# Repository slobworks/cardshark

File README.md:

<b>Update 9/17/26:</b> Big gaggle of minor changes all over. Bigger, better and cleaner PCB art on the front. Changed all those pesky 0603 0.1uF capacitors to 0805 to make them slightly less fiddly. Had to do some moderate rerouting to compensate - hopefully the 40MHz operation is not adversely affected.

CARDSHARK Tiburon v1.1 - MIT-Licensed, Open-Source Cirrus Logic CL-GD543x Based VLB VGA Card

As it says on the package. This VGA card for the VESA Local Bus supports a maximum memory size of 2MB, using traditional multiple-CAS FPM 256Kx16 SOJ memory. 70ns or faster memory is recommended, as is a CL-GD5434 chip for the fastest speed and least confusing build.
Created using KiCAD 8.0, updated for 10.0 (a thousand apologies if this breaks your older version!)

Features:
- Four layer PCB with cautiously laid ground pours, and judicious usage of stitching vias
- Beefy dedicated regulator providing analog DAC power, for further improved picture quality
- 2MB FPM memory with 64-bit data bus for CL-GD5434
- Compatible with CL-GD5430 and CL-GD5434
- Uses a 27C256-compatible UV PROM or EPROM chip for the BIOS
- Supports 40MHz VLB bus on motherboards that can actually handle that
- Mercifully short mode-switch delays on LCD monitors, unlike most vintage VGA chipsets (a Cirrus quality)
- Features my own hand-drawn artwork on back of board

Release History:
- Tiburon v1.1: Tons o' minor tweaks: bigger, better and cleaner PCB art on the front. Moved BIOS socket so I can reduce the ominous kink in the RGB traces. More forgiving 0805(2012 metric) footprints for the 0.1uF capacitors; you can still fit 0603s to them though. Moved some stuff around to try to get shorter ground loop paths when possible.
- Tiburon v1.0: First proper release.
- Tiburon Take 3 (internal): FINALLY we have a properly working VLB card... so long as you only use a GD5434 and 2MB of memory. One of the RAS lines got screwed, which gets overridden anyway when a GD5434 is used. Also some really minor bugs (wrong resistor values in a couple spots, easily fixed). At least it sure looks nice assembled, and so long as it's given a GD5434 with 2MB, it's a monster (of the good kind).
- Take 2 (internal): Almost worked. Major bugs all over the place. Barely functional.
- 0.1b: Major overhaul. Relaid everything, redid a lot of stuff that was broken and didn't work (if the previous version wasted your money... sorry! I feel like a prize horse's arse for uploading something so broken, as it is!)

Known Issues:
- Hand-soldering that PQFP-208 chip with all those thin little pins is a nightmare, even with hot air
- While generally very good, Mode 13h and EGA image quality isn't 100% perfect on LCD. Some extremely faint vertical lines, though generally much less pronounced than on extant cards; you will probably want to play with your RetroTINK's timings a bit (these seem to be timing related and not noise, as they are not visible at all in SVGA modes)
- EDO is ONLY supported on CL-GD5434-J-QC, but even then it does not improve performance at all. *NO* other versions support EDO, so don't waste money ordering EDO SOJ chips

Bill of Materials: (All passive parts are 0805/2012 metric unless otherwise indicated)
- 1x Cirrus Logic CL-GD5430 or CL-GD5434 PQFP-208 chip (watch out for fakes - they're everywhere)
- 1x SOIC-14 (3.9mm x 8.7mm P1.27mm) SN74F260DR or directly compatible part
- At least 2x, but up to 4x 256Kx16 dual-CAS Fast Page Mode (*NOT* EDO) SOJ-40 DRAM memory
- 1x 78M05 5V DPAK regulator (LF50 is compatible)
- 1x 14.318MHz DIP-14 CXO 4-pin through-hole oscillator
- 1x MMBT3904 SOT-23 NPN transistor
- 1x TL431DBZ SOT-23 programmable shunt reference
- 3x 11 ohm @ 100MHz ferrite beads (for RGB signals)
- 3x 100+ ohm @ 100MHz ferrite beads (for power rails)
- 2x 1x2 2.54mm THT pin headers + jumper caps
- 1x 2x3 1.27mm SMD pin header + jumper caps
- 4x 10pF 25/50v MLCC X5R/X7R ceramic capacitor
- 20x 0805(2012 metric) 0.1uF 25/50v MLCC X5R/X7R ceramic capacitor
- 4x 2.2uF 25/50v MLCC X5R/X7R ceramic capacitor
- 6x 10uF 25/50v MLCC X5R/X7R ceramic capacitor
- 1x 5mm 22uF 16V SMD electrolytic capacitor
- 1x 0 ohm SMD resistor (or a short snip of wire)
- 3x 0603(1608 metric) 10 ohm SMD resistors
- 1x 4x0603 33 ohm convex SMD resistor pack
- 2x 0603(1608 metric) 75 ohm SMD resistors
- 1x 4x0603 75 ohm convex SMD resistor pack
- 1x 100 ohm SMD resistor
- 3x 0603(1608 metric) 6.8K SMD resistors
- 2x 4x0603 6.8K ohm convex SMD resistor packs
- 1x 0603(1608 metric) 270-330 ohm SMD resistor, 1% thin film
- 2x 1K SMD resistors
- 1x DSUB-15-HD right angle through hole VGA connector (something akin to this: https://www.digikey.com/en/products/detail/assmann-wsw-components/A-HDF15A-KG-TAXB/1241905)
- 1x DIP-28 socket + 27C256 or compatible PROM/EEPROM/flash ROM chip for BIOS + BIOS file (figure that out yourself)

Provided under the terms of the MIT License.

As you can see I'm a bit of a neophyte when it comes to this GitHub stuff.
Expect this to change as I become more familiar with the platform.

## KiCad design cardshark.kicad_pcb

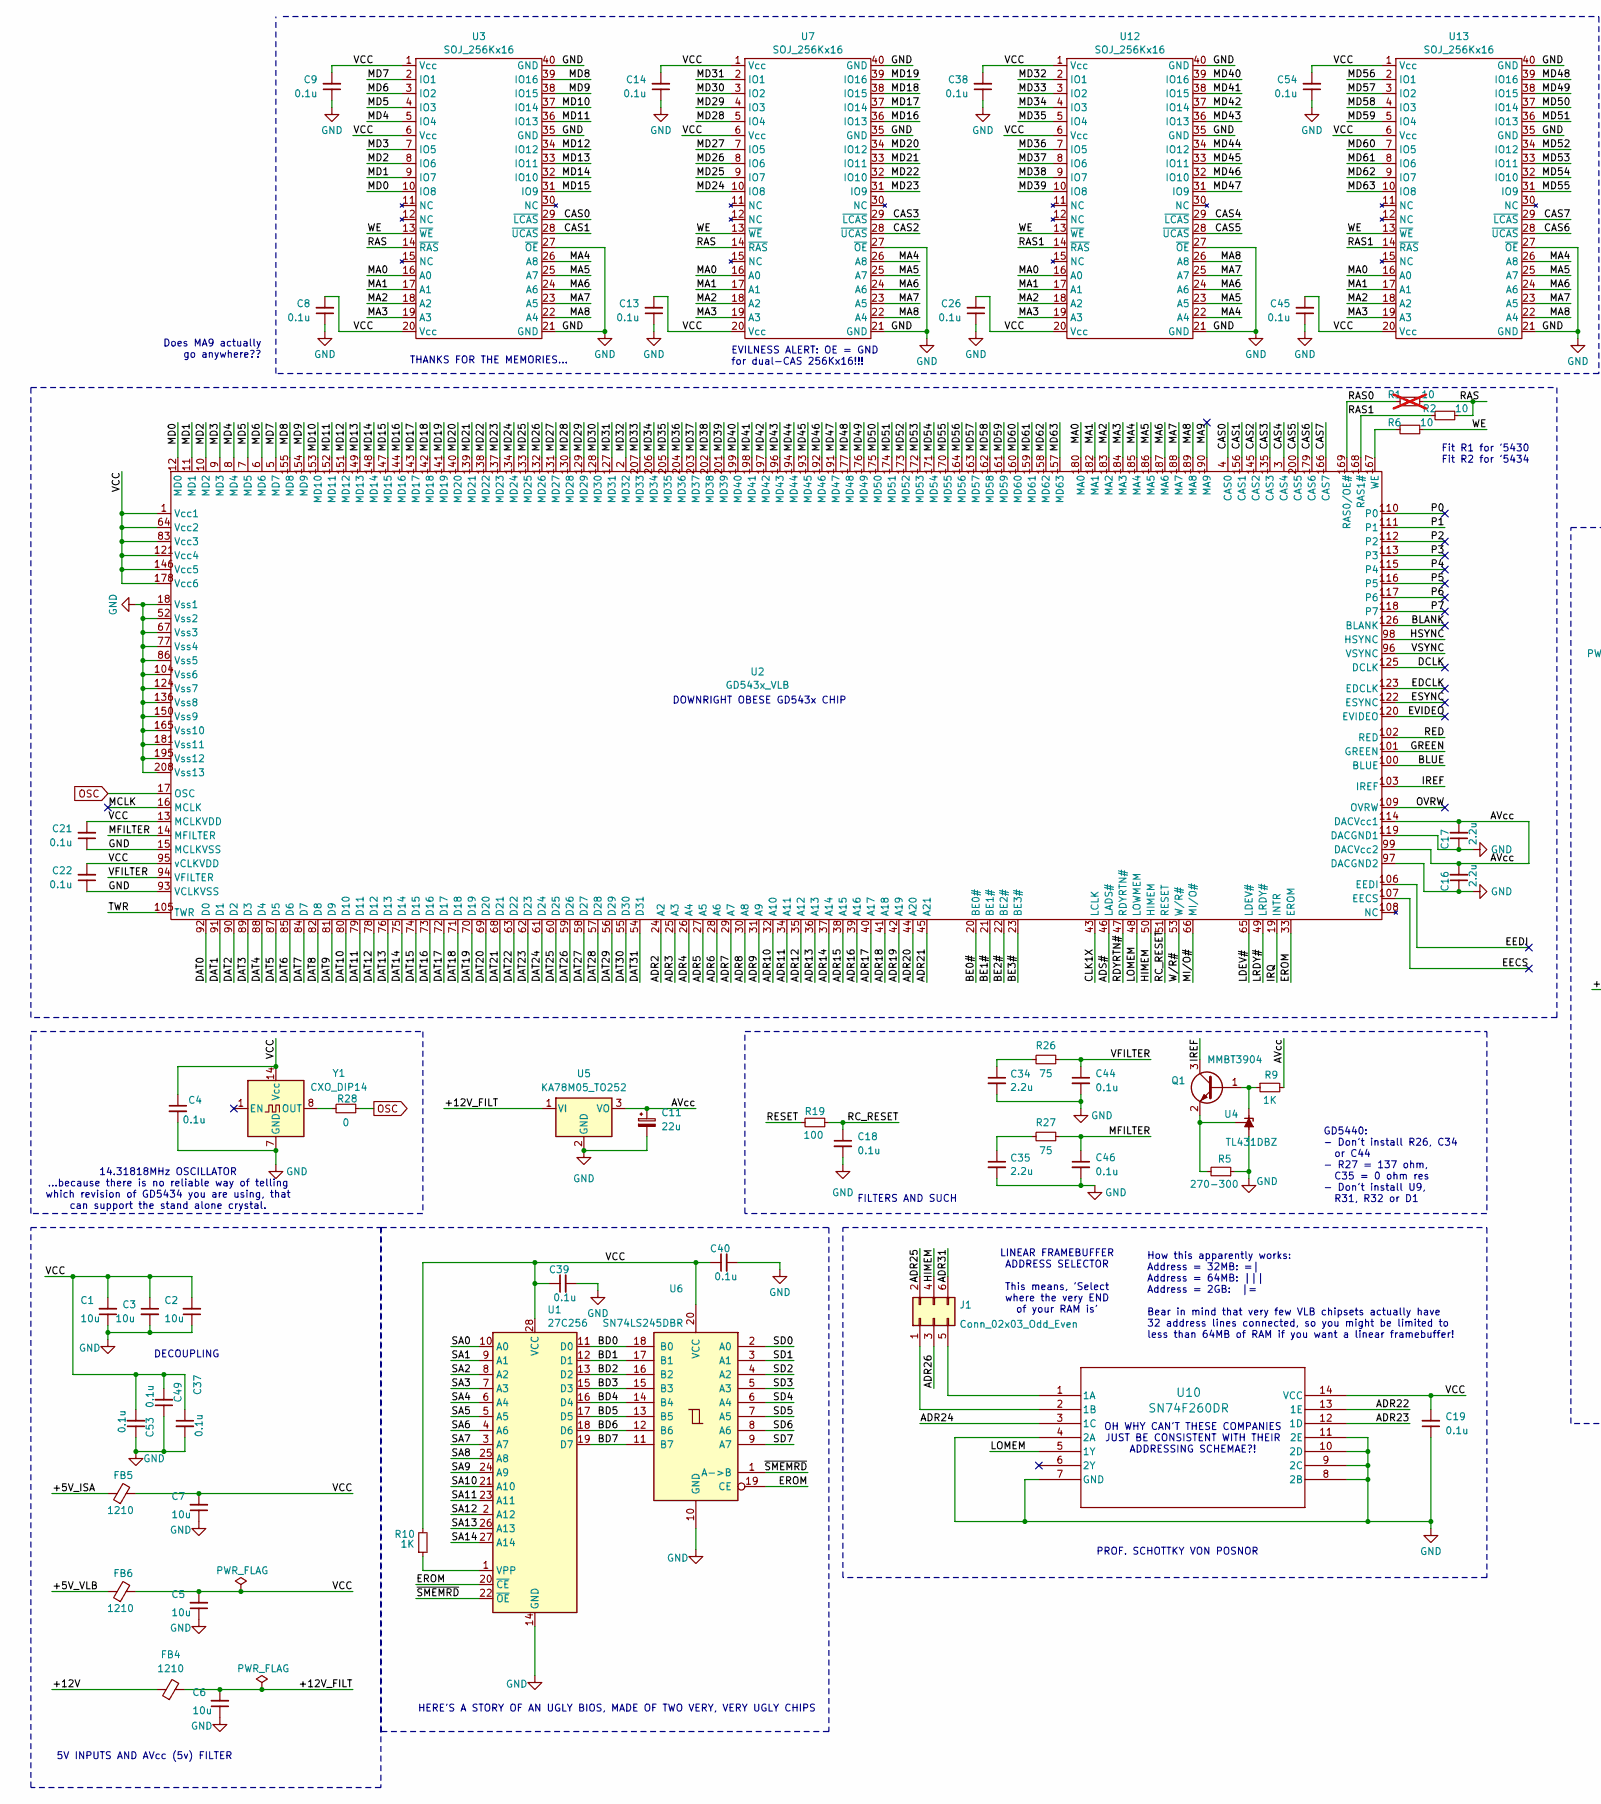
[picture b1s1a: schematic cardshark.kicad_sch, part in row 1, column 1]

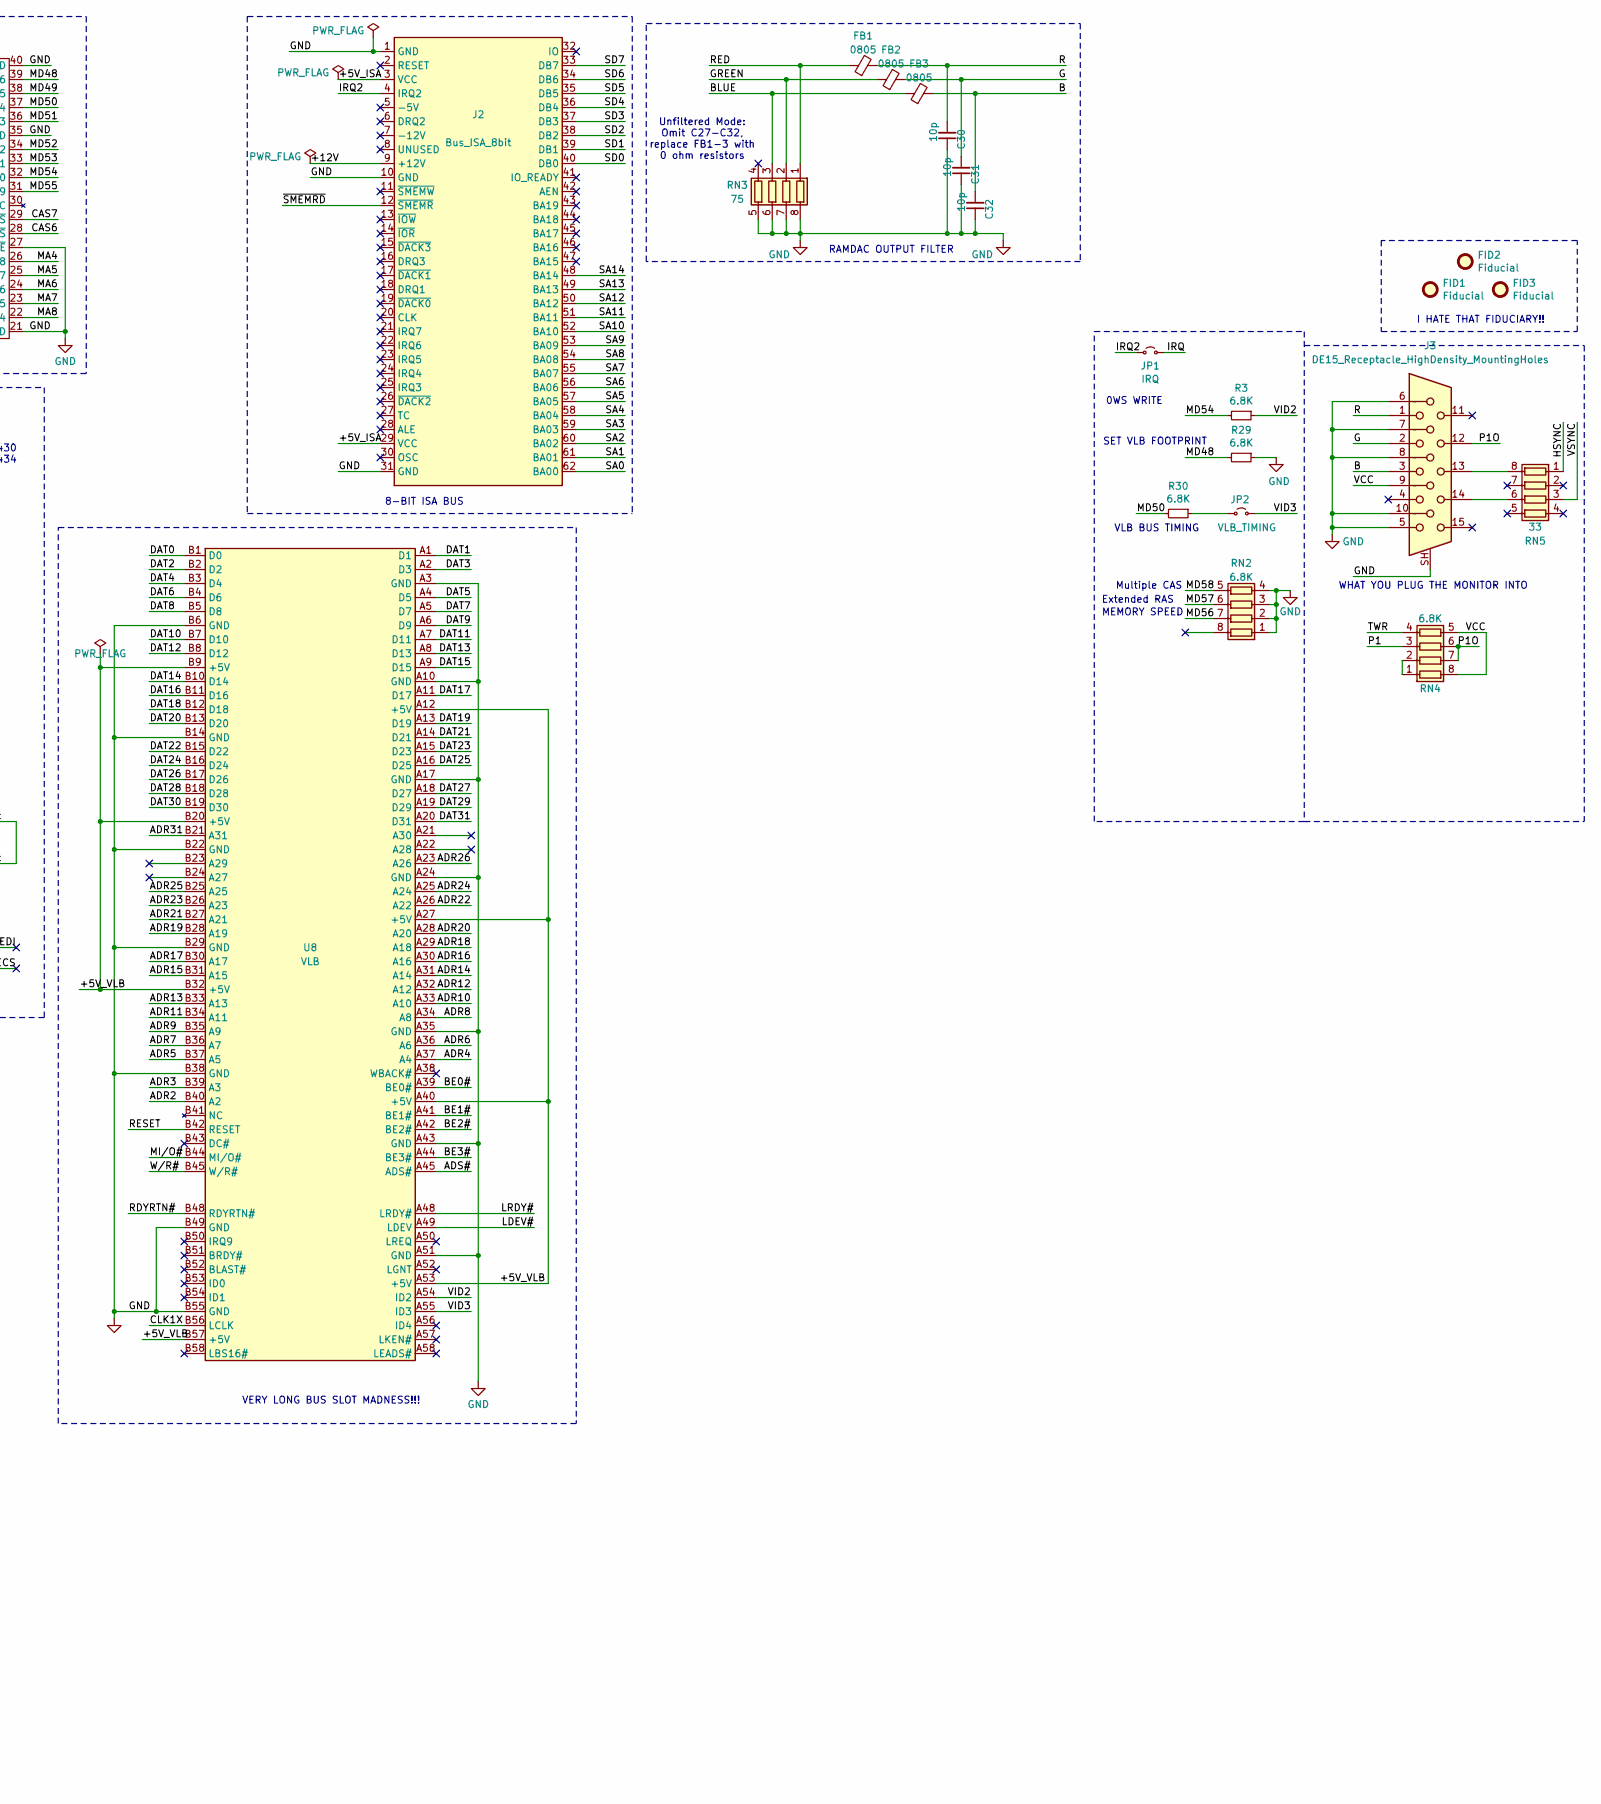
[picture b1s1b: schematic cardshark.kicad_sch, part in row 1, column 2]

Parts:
C1, C2, C3, C5, C6, C7: 10u; C_0805_2012Metric
C4, C8, C9, C13, C14, C18, C19, C21, C22, C26, C37, C38, C39, C40, C44, C45, C46, C49, C53, C54: 0.1u; C_0805_2012Metric
C11: 22u; CP_Elec_5x5.9
C16, C17, C34, C35: 2.2u; C_0805_2012Metric
C30, C31, C32: 10p; C_0805_2012Metric
FB1, FB2, FB3: 0805; L_0805_2012Metric
FB4, FB5, FB6: 1210; L_0805_2012Metric
FID1, FID2, FID3: Fiducial; Fiducial_1mm_Mask2mm
J1: Conn_02x03_Odd_Even; PinHeader_2x03_P1.27mm_Vertical_SMD
J2: Bus_ISA_8bit; ISA
J3: DE15_Receptacle_HighDensity_MountingHoles; DSUB-15-HD
JP1: IRQ; PinHeader_1x02_P2.54mm_Vertical
JP2: VLB_TIMING; PinHeader_1x02_P2.54mm_Vertical
Q1: MMBT3904; SOT-23
R1: 10; R_0603_1608Metric; not fitted
R2, R6: 10; R_0603_1608Metric
R3, R29, R30: 6.8K; R_0603_1608Metric
R5: 270-300; R_0805_2012Metric
R9, R10: 1K; R_0805_2012Metric
R19: 100; R_0805_2012Metric
R26, R27: 75; R_0805_2012Metric
R28: 0; R_0805_2012Metric
RN2, RN4: 6.8K; ResArray_Convex_4x0603
RN3: 75; ResArray_Convex_4x0603
RN5: 33; ResArray_Convex_4x0603
U1: 27C256; DIP-28_W15.24mm_Socket
U2: GD543x_VLB; PQFP-208_28x28mm_P0.5mm
U3, U7, U12, U13: SOJ_256Kx16; SOJ-40_10.16x26.44mm_P1.27mm
U4: TL431DBZ; SOT-23
U5: KA78M05_TO252; TO-252-2
U6: SN74LS245DBR; SSOP-20_5.3x7.2mm_P0.65mm
U8: VLB
U10: SN74F260DR; SOIC-14_3.9x8.7mm_P1.27mm
Y1: CXO_DIP14; Oscillator_SMD_DIP-14

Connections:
/+5V_ISA: FB5.1, J2.3 (VCC), J2.29 (VCC)
/+5V_VLB: FB6.1, U8.A12 (+5V), U8.A27 (+5V), U8.A40 (+5V), U8.A53 (+5V), U8.B9 (+5V), U8.B20 (+5V), U8.B32 (+5V), U8.B57 (+5V)
/+12V: FB4.1, J2.9 (+12V)
/+12V_FILT: C6.2, FB4.2, U5.1 (VI)
/ADR2: U2.24 (A2), U8.B40 (A2)
/ADR3: U2.25 (A3), U8.B39 (A3)
/ADR4: U2.26 (A4), U8.A37 (A4)
/ADR5: U2.27 (A5), U8.B37 (A5)
/ADR6: U2.28 (A6), U8.A36 (A6)
/ADR7: U2.29 (A7), U8.B36 (A7)
/ADR8: U2.30 (A8), U8.A34 (A8)
/ADR9: U2.31 (A9), U8.B35 (A9)
/ADR10: U2.32 (A10), U8.A33 (A10)
/ADR11: U2.34 (A11), U8.B34 (A11)
/ADR12: U2.35 (A12), U8.A32 (A12)
/ADR13: U2.36 (A13), U8.B33 (A13)
/ADR14: U2.37 (A14), U8.A31 (A14)
/ADR15: U2.38 (A15), U8.B31 (A15)
/ADR16: U2.39 (A16), U8.A30 (A16)
/ADR17: U2.40 (A17), U8.B30 (A17)
/ADR18: U2.41 (A18), U8.A29 (A18)
/ADR19: U2.42 (A19), U8.B28 (A19)
/ADR20: U2.44 (A20), U8.A28 (A20)
/ADR21: U2.45 (A21), U8.B27 (A21)
/ADR22: U8.A26 (A22), U10.13 (1E)
/ADR23: U8.B26 (A23), U10.12 (1D)
/ADR24: U8.A25 (A24), U10.3 (1C)
/ADR25: J1.2, U8.B25 (A25)
/ADR26: J1.3, U8.A23 (A26)
/ADR31: J1.6, U8.B21 (A31)
/ADS#: U2.46 (LADS#), U8.A45 (ADS#)
/AVcc: C11.1, C16.2, C17.2, R9.2, U2.99 (DACVcc2), U2.114 (DACVcc1), U5.3 (VO)
/B: C32.2, FB3.2, J3.3
/BD0: U1.11 (D0), U6.18 (B0)
/BD1: U1.12 (D1), U6.17 (B1)
/BD2: U1.13 (D2), U6.16 (B2)
/BD3: U1.15 (D3), U6.15 (B3)
/BD4: U1.16 (D4), U6.14 (B4)
/BD5: U1.17 (D5), U6.13 (B5)
/BD6: U1.18 (D6), U6.12 (B6)
/BD7: U1.19 (D7), U6.11 (B7)
/BE0#: U2.20 (BE0#), U8.A39 (BE0#)
/BE1#: U2.21 (BE1#), U8.A41 (BE1#)
/BE2#: U2.22 (BE2#), U8.A42 (BE2#)
/BE3#: U2.23 (BE3#), U8.A44 (BE3#)
/BLANK: U2.126 (BLANK)
/BLUE: FB3.1, RN3.3 (R3.1), U2.100 (BLUE)
/CAS0: U2.4 (CAS0), U3.29 (~LCAS)
/CAS1: U2.156 (CAS1), U3.28 (~UCAS)
/CAS2: U2.145 (CAS2), U7.28 (~UCAS)
/CAS3: U2.135 (CAS3), U7.29 (~LCAS)
/CAS4: U2.3 (CAS4), U12.29 (~LCAS)
/CAS5: U2.200 (CAS5), U12.28 (~UCAS)
/CAS6: U2.179 (CAS6), U13.28 (~UCAS)
/CAS7: U2.166 (CAS7), U13.29 (~LCAS)
/CLK1X: U2.43 (LCLK), U8.B56 (LCLK)
/DAT0: U2.92 (D0), U8.B1 (D0)
/DAT1: U2.91 (D1), U8.A1 (D1)
/DAT2: U2.90 (D2), U8.B2 (D2)
/DAT3: U2.89 (D3), U8.A2 (D3)
/DAT4: U2.88 (D4), U8.B3 (D4)
/DAT5: U2.87 (D5), U8.A4 (D5)
/DAT6: U2.85 (D6), U8.B4 (D6)
/DAT7: U2.84 (D7), U8.A5 (D7)
/DAT8: U2.82 (D8), U8.B5 (D8)
/DAT9: U2.81 (D9), U8.A6 (D9)
/DAT10: U2.80 (D10), U8.B7 (D10)
/DAT11: U2.79 (D11), U8.A7 (D11)
/DAT12: U2.78 (D12), U8.B8 (D12)
/DAT13: U2.76 (D13), U8.A8 (D13)
/DAT14: U2.75 (D14), U8.B10 (D14)
/DAT15: U2.74 (D15), U8.A9 (D15)
/DAT16: U2.73 (D16), U8.B11 (D16)
/DAT17: U2.72 (D17), U8.A11 (D17)
/DAT18: U2.71 (D18), U8.B12 (D18)
/DAT19: U2.70 (D19), U8.A13 (D19)
/DAT20: U2.69 (D20), U8.B13 (D20)
/DAT21: U2.68 (D21), U8.A14 (D21)
/DAT22: U2.63 (D22), U8.B15 (D22)
/DAT23: U2.62 (D23), U8.A15 (D23)
/DAT24: U2.61 (D24), U8.B16 (D24)
/DAT25: U2.60 (D25), U8.A16 (D25)
/DAT26: U2.59 (D26), U8.B17 (D26)
/DAT27: U2.58 (D27), U8.A18 (D27)
/DAT28: U2.57 (D28), U8.B18 (D28)
/DAT29: U2.56 (D29), U8.A19 (D29)
/DAT30: U2.55 (D30), U8.B19 (D30)
/DAT31: U2.54 (D31), U8.A20 (D31)
/DCLK: U2.125 (DCLK)
/EDCLK: U2.123 (EDCLK)
/EECS: U2.107 (EECS)
/EEDI: U2.106 (EEDI)
/EROM: U1.20 (~CE), U2.33 (EROM), U6.19 (CE)
/ESYNC: U2.122 (ESYNC)
/EVIDEO: U2.120 (EVIDEO)
/G: C31.2, FB2.2, J3.2
/GREEN: FB2.1, RN3.2 (R2.1), U2.101 (GREEN)
/HIMEM: J1.4, U2.50 (HIMEM)
/HSYNC: RN5.1 (R1.1), U2.98 (HSYNC)
/IREF: Q1.3 (C), U2.103 (IREF)
/IRQ: JP1.2 (B), U2.19 (INTR)
/IRQ2: J2.4 (IRQ2), JP1.1 (A)
/LDEV#: U2.65 (LDEV#), U8.A49 (LDEV)
/LOMEM: U2.48 (LOWMEM), U10.5 (1Y)
/LRDY#: U2.49 (LRDY#), U8.A48 (LRDY#)
/MA0: U2.180 (MA0), U3.16 (A0), U7.16 (A0), U12.16 (A0), U13.16 (A0)
/MA1: U2.182 (MA1), U3.17 (A1), U7.17 (A1), U12.17 (A1), U13.17 (A1)
/MA2: U2.183 (MA2), U3.18 (A2), U7.18 (A2), U12.18 (A2), U13.18 (A2)
/MA3: U2.184 (MA3), U3.19 (A3), U7.19 (A3), U12.19 (A3), U13.19 (A3)
/MA4: U2.185 (MA4), U3.26 (A8), U7.26 (A8), U12.22 (A4), U13.26 (A8)
/MA5: U2.186 (MA5), U3.25 (A7), U7.25 (A7), U12.23 (A5), U13.25 (A7)
/MA6: U2.187 (MA6), U3.24 (A6), U7.24 (A6), U12.24 (A6), U13.24 (A6)
/MA7: U2.188 (MA7), U3.23 (A5), U7.23 (A5), U12.25 (A7), U13.23 (A5)
/MA8: U2.189 (MA8), U3.22 (A4), U7.22 (A4), U12.26 (A8), U13.22 (A4)
/MA9: U2.190 (MA9)
/MCLK: U2.16 (MCLK)
/MD0: U2.12 (MD0), U3.10 (IO8)
/MD1: U2.11 (MD1), U3.9 (IO7)
/MD2: U2.10 (MD2), U3.8 (IO6)
/MD3: U2.9 (MD3), U3.7 (IO5)
/MD4: U2.8 (MD4), U3.5 (IO4)
/MD5: U2.7 (MD5), U3.4 (IO3)
/MD6: U2.6 (MD6), U3.3 (IO2)
/MD7: U2.5 (MD7), U3.2 (IO1)
/MD8: U2.155 (MD8), U3.39 (IO16)
/MD9: U2.154 (MD9), U3.38 (IO15)
/MD10: U2.153 (MD10), U3.37 (IO14)
/MD11: U2.152 (MD11), U3.36 (IO13)
/MD12: U2.151 (MD12), U3.34 (IO12)
/MD13: U2.149 (MD13), U3.33 (IO11)
/MD14: U2.148 (MD14), U3.32 (IO10)
/MD15: U2.147 (MD15), U3.31 (IO9)
/MD16: U2.144 (MD16), U7.36 (IO13)
/MD17: U2.143 (MD17), U7.37 (IO14)
/MD18: U2.142 (MD18), U7.38 (IO15)
/MD19: U2.141 (MD19), U7.39 (IO16)
/MD20: U2.140 (MD20), U7.34 (IO12)
/MD21: U2.139 (MD21), U7.33 (IO11)
/MD22: U2.138 (MD22), U7.32 (IO10)
/MD23: U2.137 (MD23), U7.31 (IO9)
/MD24: U2.134 (MD24), U7.10 (IO8)
/MD25: U2.133 (MD25), U7.9 (IO7)
/MD26: U2.132 (MD26), U7.8 (IO6)
/MD27: U2.131 (MD27), U7.7 (IO5)
/MD28: U2.130 (MD28), U7.5 (IO4)
/MD29: U2.129 (MD29), U7.4 (IO3)
/MD30: U2.128 (MD30), U7.3 (IO2)
/MD31: U2.127 (MD31), U7.2 (IO1)
/MD32: U2.2 (MD32), U12.2 (IO1)
/MD33: U2.207 (MD33), U12.3 (IO2)
/MD34: U2.206 (MD34), U12.4 (IO3)
/MD35: U2.205 (MD35), U12.5 (IO4)
/MD36: U2.204 (MD36), U12.7 (IO5)
/MD37: U2.203 (MD37), U12.8 (IO6)
/MD38: U2.202 (MD38), U12.9 (IO7)
/MD39: U2.201 (MD39), U12.10 (IO8)
/MD40: U2.199 (MD40), U12.39 (IO16)
/MD41: U2.198 (MD41), U12.38 (IO15)
/MD42: U2.197 (MD42), U12.37 (IO14)
/MD43: U2.196 (MD43), U12.36 (IO13)
/MD44: U2.194 (MD44), U12.34 (IO12)
/MD45: U2.193 (MD45), U12.33 (IO11)
/MD46: U2.192 (MD46), U12.32 (IO10)
/MD47: U2.191 (MD47), U12.31 (IO9)
/MD48: R29.2, U2.177 (MD48), U13.39 (IO16)
/MD49: U2.176 (MD49), U13.38 (IO15)
/MD50: R30.2, U2.175 (MD50), U13.37 (IO14)
/MD51: U2.174 (MD51), U13.36 (IO13)
/MD52: U2.173 (MD52), U13.34 (IO12)
/MD53: U2.172 (MD53), U13.33 (IO11)
/MD54: R3.2, U2.171 (MD54), U13.32 (IO10)
/MD55: U2.170 (MD55), U13.31 (IO9)
/MD56: RN2.7 (R2.2), U2.164 (MD56), U13.2 (IO1)
/MD57: RN2.6 (R3.2), U2.163 (MD57), U13.3 (IO2)
/MD58: RN2.5 (R4.2), U2.162 (MD58), U13.4 (IO3)
/MD59: U2.161 (MD59), U13.5 (IO4)
/MD60: U2.160 (MD60), U13.7 (IO5)
/MD61: U2.159 (MD61), U13.8 (IO6)
/MD62: U2.158 (MD62), U13.9 (IO7)
/MD63: U2.157 (MD63), U13.10 (IO8)
/MFILTER: C46.1, R27.1, U2.14 (MFILTER)
/MI/O#: U2.66 (MI/O#), U8.B44 (MI/O#)
/OVRW: U2.109 (OVRW)
/P0: U2.110 (P0)
/P1: RN4.3 (R3.1), U2.111 (P1)
/P1O: J3.12, RN4.6 (R3.2), RN4.7 (R2.2)
/P2: U2.112 (P2)
/P3: U2.113 (P3)
/P4: U2.115 (P4)
/P5: U2.116 (P5)
/P6: U2.117 (P6)
/P7: U2.118 (P7)
/R: C30.2, FB1.2, J3.1
/RAS: R1.1, R2.1, U3.14 (~RAS), U7.14 (~RAS)
/RAS0: R1.2, U2.169 (RAS0/OE#)
/RAS1: R2.2, U2.168 (RAS1#), U12.14 (~RAS), U13.14 (~RAS)
/RC_RESET: C18.1, R19.1, U2.51 (RESET)
/RDYRTN#: U2.47 (RDYRTN#), U8.B48 (RDYRTN#)
/RED: FB1.1, RN3.1 (R1.1), U2.102 (RED)
/RESET: R19.2, U8.B42 (RESET)
/SA0: J2.62 (BA00), U1.10 (A0)
/SA1: J2.61 (BA01), U1.9 (A1)
/SA2: J2.60 (BA02), U1.8 (A2)
/SA3: J2.59 (BA03), U1.7 (A3)
/SA4: J2.58 (BA04), U1.6 (A4)
/SA5: J2.57 (BA05), U1.5 (A5)
/SA6: J2.56 (BA06), U1.4 (A6)
/SA7: J2.55 (BA07), U1.3 (A7)
/SA8: J2.54 (BA08), U1.25 (A8)
/SA9: J2.53 (BA09), U1.24 (A9)
/SA10: J2.52 (BA10), U1.21 (A10)
/SA11: J2.51 (BA11), U1.23 (A11)
/SA12: J2.50 (BA12), U1.2 (A12)
/SA13: J2.49 (BA13), U1.26 (A13)
/SA14: J2.48 (BA14), U1.27 (A14)
/SD0: J2.40 (DB0), U6.2 (A0)
/SD1: J2.39 (DB1), U6.3 (A1)
/SD2: J2.38 (DB2), U6.4 (A2)
/SD3: J2.37 (DB3), U6.5 (A3)
/SD4: J2.36 (DB4), U6.6 (A4)
/SD5: J2.35 (DB5), U6.7 (A5)
/SD6: J2.34 (DB6), U6.8 (A6)
/SD7: J2.33 (DB7), U6.9 (A7)
/TWR: RN4.4 (R4.1), U2.105 (TWR)
/VCC: C1.2, C2.2, C3.1, C4.1, C5.2, C7.2, C8.2, C9.2, C13.2, C14.2, C19.2, C21.2, C22.2, C26.2, C37.1, C38.2, C39.1, C40.1, C45.2, C49.2, C53.2, C54.2, FB5.2, FB6.2, J3.9, R10.2, RN4.5 (R4.2), RN4.8 (R1.2), U1.28 (VCC), U2.1 (Vcc1), U2.13 (MCLKVDD), U2.64 (Vcc2), U2.83 (Vcc3), U2.95 (vCLKVDD), U2.121 (Vcc4), U2.146 (Vcc5), U2.178 (Vcc6), U3.1 (Vcc), U3.6 (Vcc), U3.20 (Vcc), U6.20 (VCC), U7.1 (Vcc), U7.6 (Vcc), U7.20 (Vcc), U10.14 (VCC), U12.1 (Vcc), U12.6 (Vcc), U12.20 (Vcc), U13.1 (Vcc), U13.6 (Vcc), U13.20 (Vcc), Y1.14 (Vcc)
/VFILTER: C44.1, R26.1, U2.94 (VFILTER)
/VID2: R3.1, U8.A54 (ID2)
/VID3: JP2.2 (B), U8.A55 (ID3)
/VSYNC: RN5.3 (R3.1), U2.96 (VSYNC)
/WE: R6.1, U3.13 (~WE), U7.13 (~WE), U12.13 (~WE), U13.13 (~WE)
/W/R#: U2.53 (W/R#), U8.B45 (W/R#)
/~SMEMRD: J2.12 (~SMEMR), U1.22 (~OE), U6.1 (A->B)
GND: C1.1, C2.1, C3.2, C4.2, C5.1, C6.1, C7.1, C8.1, C9.1, C11.2, C13.1, C14.1, C16.1, C17.1, C18.2, C19.1, C21.1, C22.1, C26.1, C30.1, C31.1, C32.1, C34.2, C35.2, C37.2, C38.1, C39.2, C40.2, C44.2, C45.1, C46.2, C49.1, C53.1, C54.1, J2.1 (GND), J2.10 (GND), J2.31 (GND), J3.5, J3.6, J3.7, J3.8, J3.10, J3.SH, R5.1, R29.1, RN2.1 (R1.1), RN2.2 (R2.1), RN2.3 (R3.1), RN2.4 (R4.1), RN3.5 (R4.2), RN3.6 (R3.2), RN3.7 (R2.2), RN3.8 (R1.2), U1.14 (GND), U2.15 (MCLKVSS), U2.18 (Vss1), U2.52 (Vss2), U2.67 (Vss3), U2.77 (Vss4), U2.86 (Vss5), U2.93 (VCLKVSS), U2.97 (DACGND2), U2.104 (Vss6), U2.119 (DACGND1), U2.124 (Vss7), U2.136 (Vss8), U2.150 (Vss9), U2.165 (Vss10), U2.181 (Vss11), U2.195 (Vss12), U2.208 (Vss13), U3.21 (GND), U3.27 (~OE), U3.35 (GND), U3.40 (GND), U4.3 (A), U5.2 (GND), U6.10 (GND), U7.21 (GND), U7.27 (~OE), U7.35 (GND), U7.40 (GND), U8.A3 (GND), U8.A10 (GND), U8.A17 (GND), U8.A24 (GND), U8.A35 (GND), U8.A43 (GND), U8.A51 (GND), U8.B6 (GND), U8.B14 (GND), U8.B22 (GND), U8.B29 (GND), U8.B38 (GND), U8.B49 (GND), U8.B55 (GND), U10.4 (2A), U10.7 (GND), U10.8 (2B), U10.9 (2C), U10.10 (2D), U10.11 (2E), U12.21 (GND), U12.27 (~OE), U12.35 (GND), U12.40 (GND), U13.21 (GND), U13.27 (~OE), U13.35 (GND), U13.40 (GND), Y1.7 (GND)
unnamed: C34.1, R26.2
unnamed: C35.1, R27.2
unnamed: J1.1, U10.2 (1B)
unnamed: J1.5, U10.1 (1A)
unnamed: JP2.1 (A), R30.1
unnamed: Q1.1 (B), R9.1, U4.1 (K)
unnamed: Q1.2 (E), R5.2, U4.2 (REF)
unnamed: RN4.1 (R1.1), RN4.2 (R2.1)
unnamed: J3.13, RN5.8 (R1.2)
unnamed: J3.14, RN5.6 (R3.2)
unnamed: R10.1, U1.1 (VPP)
unnamed: R6.2, U2.167 (WE)
unnamed: R28.2, Y1.8 (OUT)
OSC: R28.1, U2.17 (OSC)

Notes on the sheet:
Unfiltered Mode: Omit C27-C32, replace FB1-3 with 0 ohm resistors
GD5440: - Don't install R26, C34 or C44 - R27 = 137 ohm, C35 = 0 ohm res - Don't install U9, R31, R32 or D1
8-BIT ISA BUS
OH WHY CAN'T THESE COMPANIES JUST BE CONSISTENT WITH THEIR ADDRESSING SCHEMAE?!
HERE'S A STORY OF AN UGLY BIOS, MADE OF TWO VERY, VERY UGLY CHIPS
Multiple CAS
FILTERS AND SUCH
How this apparently works: Address = 32MB: =| Address = 64MB: ||| Address = 2GB: |= Bear in mind that very few VLB chipsets actually have 32 address lines connected, so you might be limited to less than 64MB of RAM if you want a linear framebuffer!
0WS WRITE
VLB BUS TIMING
14.31818MHz OSCILLATOR ...because there is no reliable way of telling which revision of GD5434 you are using, that can support the stand alone crystal.
Fit R1 for '5430 Fit R2 for '5434
Does MA9 actually go anywhere??
THANKS FOR THE MEMORIES...
DOWNRIGHT OBESE GD543x CHIP
VERY LONG BUS SLOT MADNESS!!!
MEMORY SPEED
5V INPUTS AND AVcc (5v) FILTER
SET VLB FOOTPRINT
WHAT YOU PLUG THE MONITOR INTO
LINEAR FRAMEBUFFER ADDRESS SELECTOR This means, 'Select where the very END of your RAM is'
RAMDAC OUTPUT FILTER
I HATE THAT FIDUCIARY!!
Extended RAS
DECOUPLING
PROF. SCHOTTKY VON POSNOR
EVILNESS ALERT: OE = GND for dual-CAS 256Kx16!!!

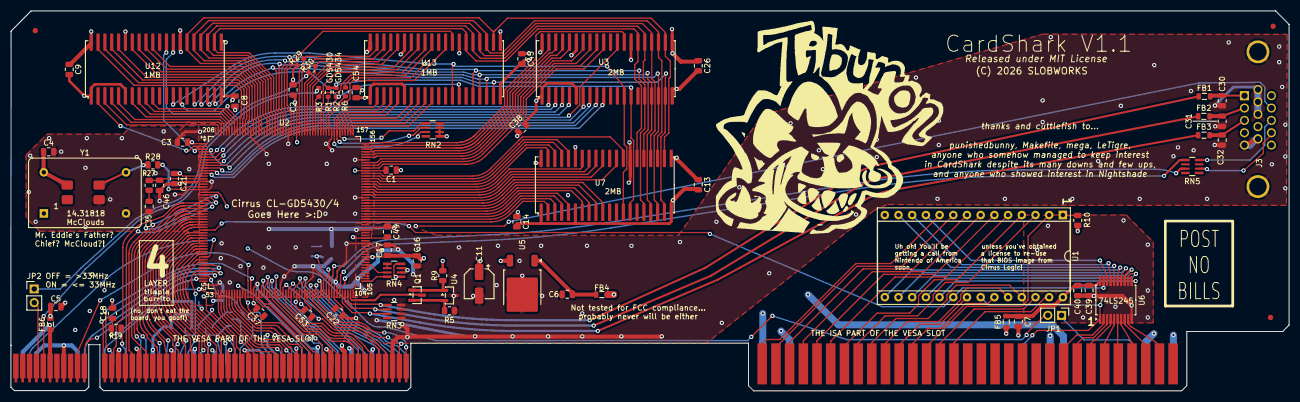
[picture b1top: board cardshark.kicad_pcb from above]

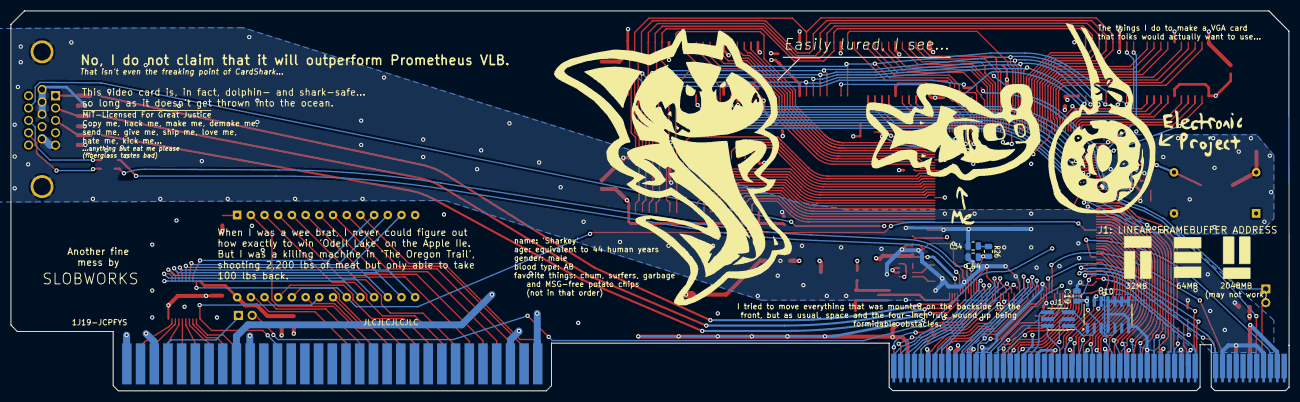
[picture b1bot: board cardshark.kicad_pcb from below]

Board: 4 copper layers, 237.0 x 70.4 mm, 78 parts (6 on the bottom side), 230 nets.

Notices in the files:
cardshark-isa.kicad_pcb:
Released under MIT License
(C)2025, SLOBWORKS
cardshark.kicad_pcb:
(C) 2026 SLOBWORKS
